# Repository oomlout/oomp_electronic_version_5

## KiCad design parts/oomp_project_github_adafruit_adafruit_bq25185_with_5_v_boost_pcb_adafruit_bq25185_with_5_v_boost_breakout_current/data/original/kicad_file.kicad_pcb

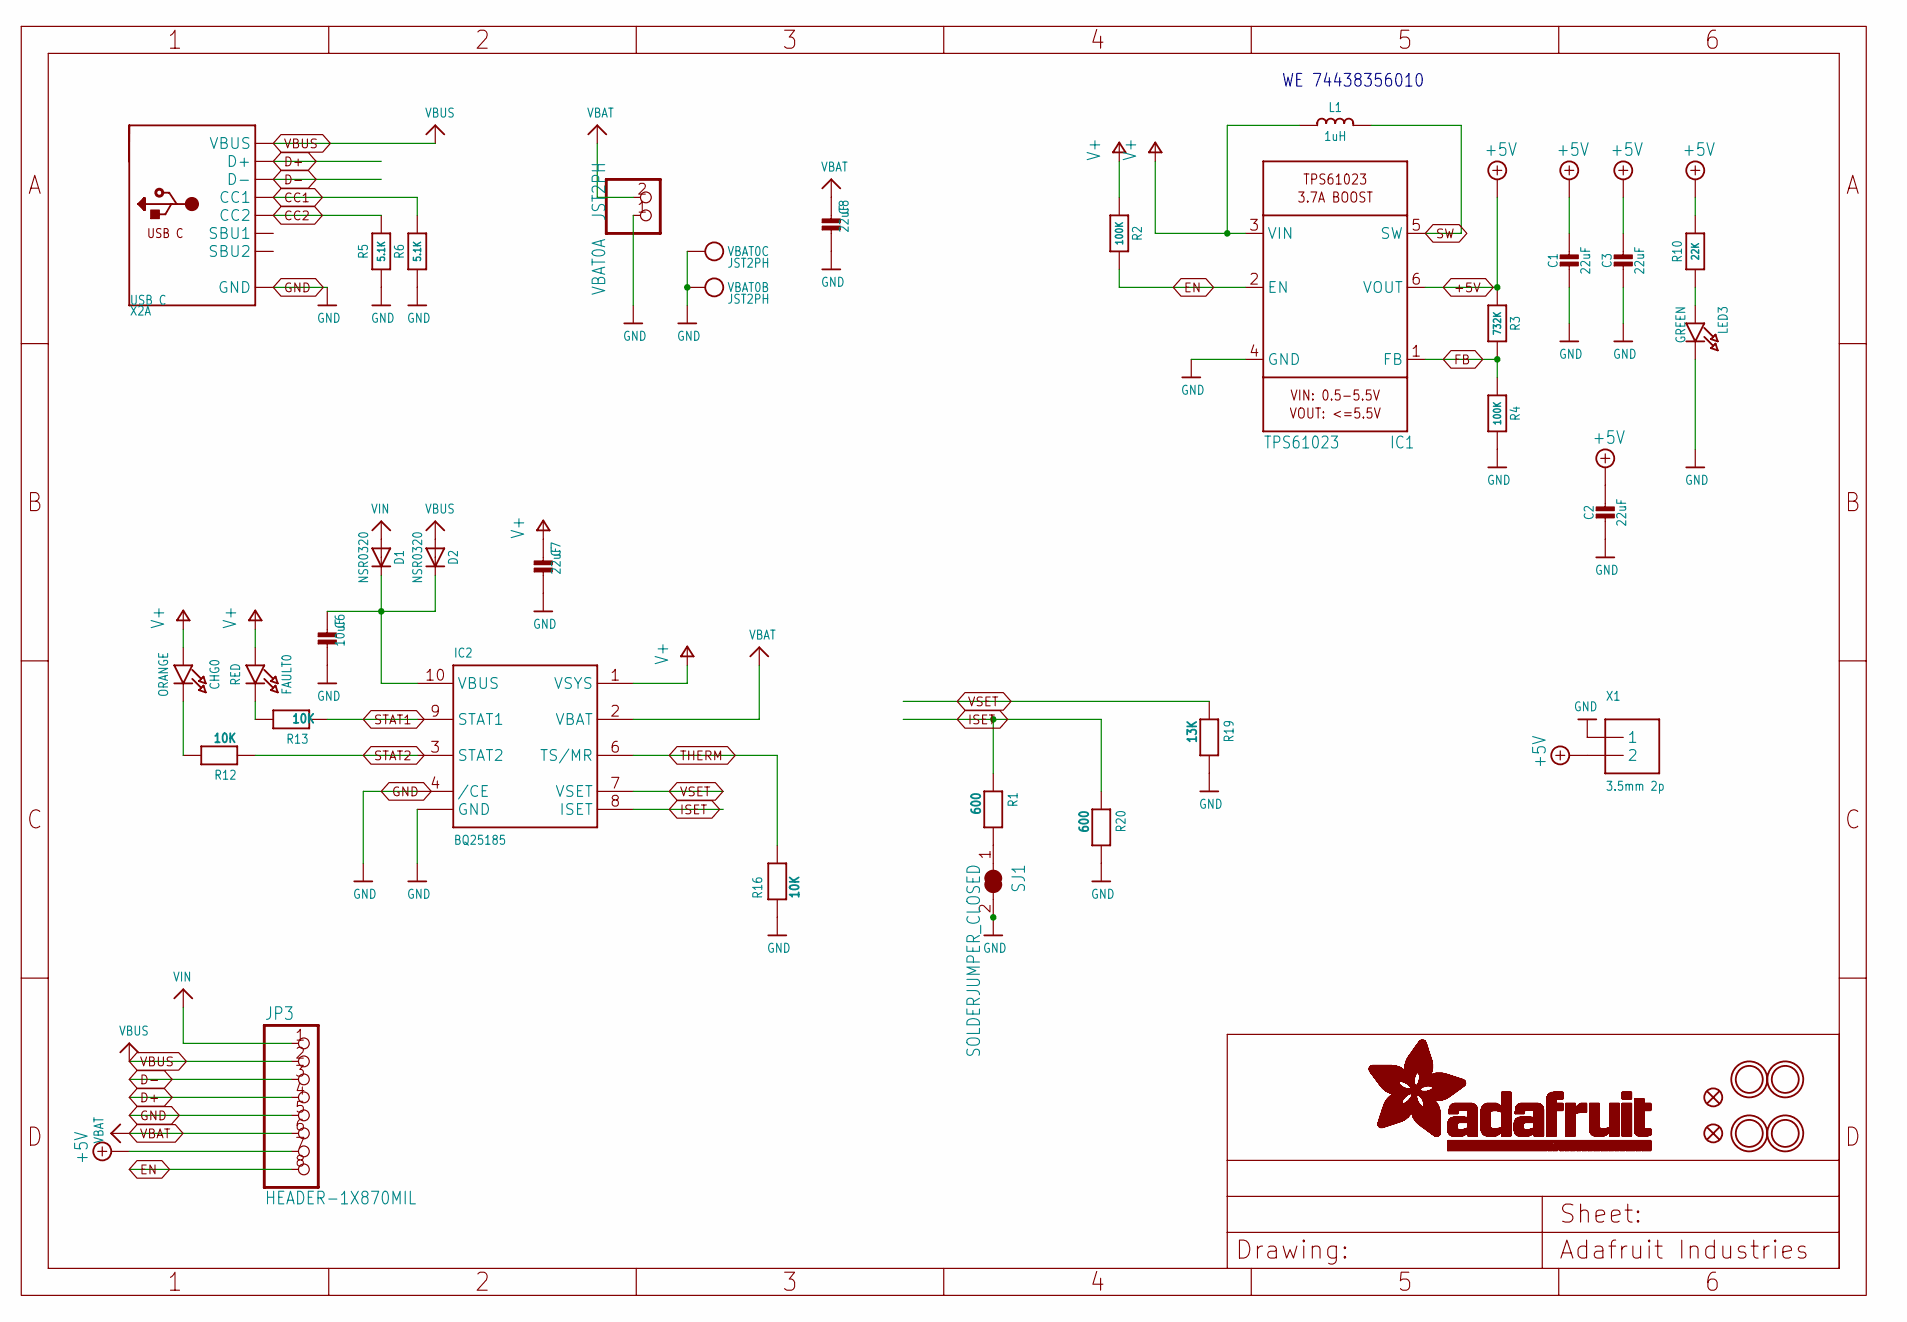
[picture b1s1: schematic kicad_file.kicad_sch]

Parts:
C1, C2, C3, C7, C8: 22uF; 0805-NO
C6: 10uF; 0805-NO
CHG0: ORANGE; CHIPLED_0603_NOOUTLINE
D1, D2: NSR0320; SOD-323_MINI
FAULT0: RED; CHIPLED_0603_NOOUTLINE
FID1, FID2: FIDUCIAL_0.5MM
IC1: TPS61023; SOT563
IC2: BQ25185; WSON10
JP3: HEADER-1X870MIL; 1X08_ROUND_70
L1: 1uH; INDUCTOR_5045_SMALLTABS
LED3: GREEN; CHIPLED_0603_NOOUTLINE
R1, R20: 600; _0402NO
R2, R4: 100K; _0402NO
R3: 732K; _0402NO
R5, R6: 5.1K; _0402NO
R10: 22K; _0402NO
R12, R13, R16: 10K; _0402NO
R19: 13K; _0402NO
SJ1: SOLDERJUMPER_CLOSED; SOLDERJUMPER_CLOSEDWIRE
U$9, U$10, U$11, U$12: MOUNTINGHOLE2.5; MOUNTINGHOLE_2.5_PLATED
VBAT0: JST2PH; JSTPH2_BATT; LCSC C47647
X1: 3.5mm 2p; TERMBLOCK_1X2-3.5MM
X2: USB C; USB_C_CUSB31-CFM2AX-01-X; LCSC C165948

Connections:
+5V: C1.1, C2.1, C3.1, IC1.6 (VOUT), JP3.7, R3.1, R10.2, X1.2
CC1: R6.2, X2.A5 (CC1)
CC2: R5.2, X2.B5 (CC2)
D+: JP3.4, X2.A6 (D+), X2.B6 (D+)
D-: JP3.3, X2.A7 (D-), X2.B7 (D-)
EN: IC1.2 (EN), JP3.8, R2.2
FB: IC1.1 (FB), R3.2, R4.1
GND: C1.2, C2.2, C3.2, C6.2, C7.2, C8.2, IC1.4 (GND), IC2.4 (/CE), IC2.5 (GND), IC2.PAD (GND), JP3.5, LED3.C, R4.2, R5.1, R6.1, R16.1, R19.2, R20.2, SJ1.2, VBAT0.1, VBAT0.NC1, VBAT0.NC2, X1.1, X2.A1B12 (GND), X2.B1A12 (GND)
ISET: IC2.8 (ISET), R1.1, R20.1
unnamed: R1.2, SJ1.1
unnamed: C6.1, D1.C, D2.C, IC2.10 (VBUS)
unnamed: CHG0.C, R12.2
unnamed: LED3.A, R10.1
unnamed: FAULT0.C, R13.2
STAT1: IC2.9 (STAT1), R13.1
STAT2: IC2.3 (STAT2), R12.1
SW: IC1.5 (SW), L1.2
THERM: IC2.6 (TS/MR), R16.2
V+: C7.1, CHG0.A, FAULT0.A, IC1.3 (VIN), IC2.1 (VSYS), L1.1, R2.1
VBAT: C8.1, IC2.2 (VBAT), JP3.6, VBAT0.2
VBUS: D2.A, JP3.2, X2.A4B9 (VBUS), X2.B4A9 (VBUS)
VIN: D1.A, JP3.1
VSET: IC2.7 (VSET), R19.1

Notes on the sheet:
WE 74438356010

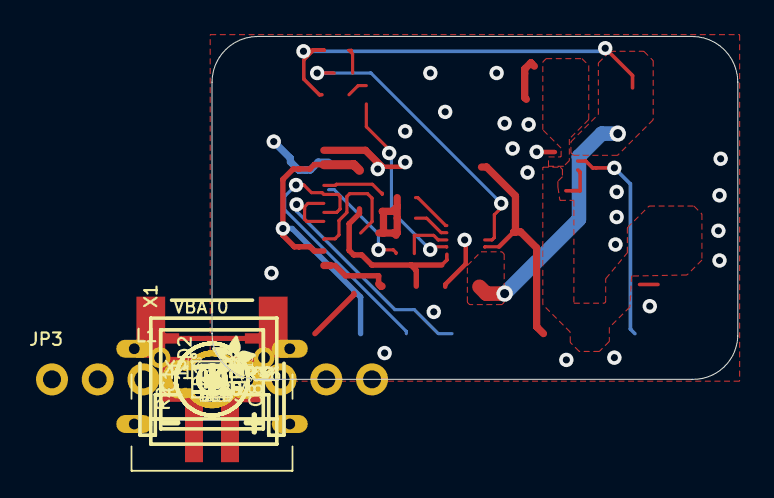
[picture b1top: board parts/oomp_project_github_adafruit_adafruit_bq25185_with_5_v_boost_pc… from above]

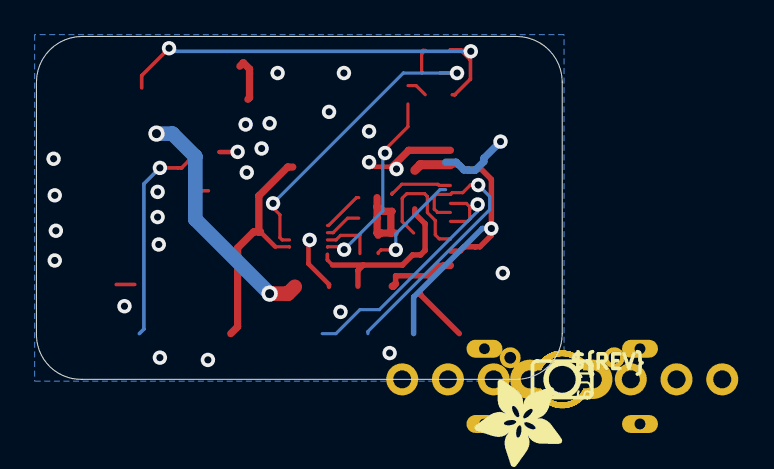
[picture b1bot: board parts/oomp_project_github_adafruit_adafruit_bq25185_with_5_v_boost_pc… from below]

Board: 2 copper layers, 29.2 x 19.1 mm, 66 parts (16 on the bottom side), 23 nets.

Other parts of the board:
PLABEL0: PLABEL0
PLABEL1: PLABEL1
PLABEL2: PLABEL2
PLABEL3: PLABEL3
PLABEL4: PLABEL4
PLABEL5: PLABEL5
PLABEL6: PLABEL6
PLABEL7: PLABEL7
PLABEL8: PLABEL8
PLABEL9: PLABEL9
PLABEL10: PLABEL10
PLABEL12: PLABEL12
PLABEL13: PLABEL13
PLABEL16: PLABEL16
PLABEL17: PLABEL17
PLABEL18: PLABEL18
PLABEL19: PLABEL19
PLABEL20: PLABEL20
PLABEL21: PLABEL21
PLABEL22: PLABEL22
PLABEL23: PLABEL23
PLABEL24: PLABEL24
PLABEL25: PLABEL25
PLABEL26: PLABEL26
U$2: PCBFEAT-REV-040
U$3: SYMBOL_PLUS
U$4: SYMBOL_MINUS
U$26: ADAFRUIT_5MM
U$34: ADAFRUIT_2.5MM

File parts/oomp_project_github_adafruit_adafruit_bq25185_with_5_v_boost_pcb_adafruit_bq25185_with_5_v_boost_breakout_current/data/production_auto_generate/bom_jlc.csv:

Comment,Designator,Footprint,LCSC Part #
,JP3,Adafruit bq25185 with 5V Boost Breakout-import-fps:1X08_ROUND_70,C492421
,U$34,Adafruit bq25185 with 5V Boost Breakout-import-fps:ADAFRUIT_2.5MM,
,U$26,Adafruit bq25185 with 5V Boost Breakout-import-fps:ADAFRUIT_5MM,
,U$2,Adafruit bq25185 with 5V Boost Breakout-import-fps:PCBFEAT-REV-040,
,PLABEL0,Adafruit bq25185 with 5V Boost Breakout-import-fps:PLABEL0,
,PLABEL1,Adafruit bq25185 with 5V Boost Breakout-import-fps:PLABEL1,
,PLABEL10,Adafruit bq25185 with 5V Boost Breakout-import-fps:PLABEL10,
,PLABEL12,Adafruit bq25185 with 5V Boost Breakout-import-fps:PLABEL12,
,PLABEL13,Adafruit bq25185 with 5V Boost Breakout-import-fps:PLABEL13,
,PLABEL16,Adafruit bq25185 with 5V Boost Breakout-import-fps:PLABEL16,
,PLABEL17,Adafruit bq25185 with 5V Boost Breakout-import-fps:PLABEL17,
,PLABEL18,Adafruit bq25185 with 5V Boost Breakout-import-fps:PLABEL18,
,PLABEL19,Adafruit bq25185 with 5V Boost Breakout-import-fps:PLABEL19,
,PLABEL2,Adafruit bq25185 with 5V Boost Breakout-import-fps:PLABEL2,
,PLABEL20,Adafruit bq25185 with 5V Boost Breakout-import-fps:PLABEL20,
,PLABEL21,Adafruit bq25185 with 5V Boost Breakout-import-fps:PLABEL21,
,PLABEL22,Adafruit bq25185 with 5V Boost Breakout-import-fps:PLABEL22,
,PLABEL23,Adafruit bq25185 with 5V Boost Breakout-import-fps:PLABEL23,
,PLABEL24,Adafruit bq25185 with 5V Boost Breakout-import-fps:PLABEL24,
,PLABEL25,Adafruit bq25185 with 5V Boost Breakout-import-fps:PLABEL25,
,PLABEL26,Adafruit bq25185 with 5V Boost Breakout-import-fps:PLABEL26,
,PLABEL3,Adafruit bq25185 with 5V Boost Breakout-import-fps:PLABEL3,
,PLABEL4,Adafruit bq25185 with 5V Boost Breakout-import-fps:PLABEL4,
,PLABEL5,Adafruit bq25185 with 5V Boost Breakout-import-fps:PLABEL5,
,PLABEL6,Adafruit bq25185 with 5V Boost Breakout-import-fps:PLABEL6,
,PLABEL7,Adafruit bq25185 with 5V Boost Breakout-import-fps:PLABEL7,
,PLABEL8,Adafruit bq25185 with 5V Boost Breakout-import-fps:PLABEL8,
,PLABEL9,Adafruit bq25185 with 5V Boost Breakout-import-fps:PLABEL9,
,U$4,Adafruit bq25185 with 5V Boost Breakout-import-fps:SYMBOL_MINUS,
,U$3,Adafruit bq25185 with 5V Boost Breakout-import-fps:SYMBOL_PLUS,
100K,"R2,R4",Adafruit bq25185 with 5V Boost Breakout-import-fps:_0402NO,C25530
10K,"R12,R13,R16",Adafruit bq25185 with 5V Boost Breakout-import-fps:_0402NO,C2906861
10uF,C6,Adafruit bq25185 with 5V Boost Breakout-import-fps:0805-NO,
13K,R19,Adafruit bq25185 with 5V Boost Breakout-import-fps:_0402NO,
1uH,L1,Adafruit bq25185 with 5V Boost Breakout-import-fps:INDUCTOR_5045_SMALLTABS,
22K,R10,Adafruit bq25185 with 5V Boost Breakout-import-fps:_0402NO,C82868
22uF,"C1,C2,C3,C7,C8",Adafruit bq25185 with 5V Boost Breakout-import-fps:0805-NO,
3.5mm 2p,X1,Adafruit bq25185 with 5V Boost Breakout-import-fps:TERMBLOCK_1X2-3.5MM,
5.1K,"R5,R6",Adafruit bq25185 with 5V Boost Breakout-import-fps:_0402NO,C25905
600,"R1,R20",Adafruit bq25185 with 5V Boost Breakout-import-fps:_0402NO,
732K,R3,Adafruit bq25185 with 5V Boost Breakout-import-fps:_0402NO,
BQ25185,IC2,Adafruit bq25185 with 5V Boost Breakout-import-fps:WSON10,
GREEN,LED3,Adafruit bq25185 with 5V Boost Breakout-import-fps:CHIPLED_0603_NOOUTLINE,
JST2PH,VBAT0,Adafruit bq25185 with 5V Boost Breakout-import-fps:JSTPH2_BATT,
NSR0320,"D1,D2",Adafruit bq25185 with 5V Boost Breakout-import-fps:SOD-323_MINI,
ORANGE,CHG0,Adafruit bq25185 with 5V Boost Breakout-import-fps:CHIPLED_0603_NOOUTLINE,
RED,FAULT0,Adafruit bq25185 with 5V Boost Breakout-import-fps:CHIPLED_0603_NOOUTLINE,
TPS61023,IC1,Adafruit bq25185 with 5V Boost Breakout-import-fps:SOT563,
USB C,X2,Adafruit bq25185 with 5V Boost Breakout-import-fps:USB_C_CUSB31-CFM2AX-01-X,

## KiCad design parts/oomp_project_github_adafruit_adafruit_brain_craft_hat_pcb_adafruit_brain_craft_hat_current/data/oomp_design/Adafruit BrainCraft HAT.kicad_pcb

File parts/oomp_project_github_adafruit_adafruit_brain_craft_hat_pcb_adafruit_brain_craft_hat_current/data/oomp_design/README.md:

# OOMP KiCad design copy

Open `Adafruit BrainCraft HAT.kicad_pro` (or the `.kicad_pcb` / `.kicad_sch`) in KiCad. Local OOMP libraries are under `libraries/`. Original inputs are preserved in [../original/](../original/).

Only verified unchanged installed KiCad defaults were renamed. Modified, custom, unmatched and unavailable items remain unchanged. Soldering variants are never swapped during conversion. Existing pad coordinates, nets and UUIDs are preserved.

See [conversion_report.yaml](conversion_report.yaml) for every conversion and skip. Copy this directory before editing; regeneration refuses to overwrite edited design files.

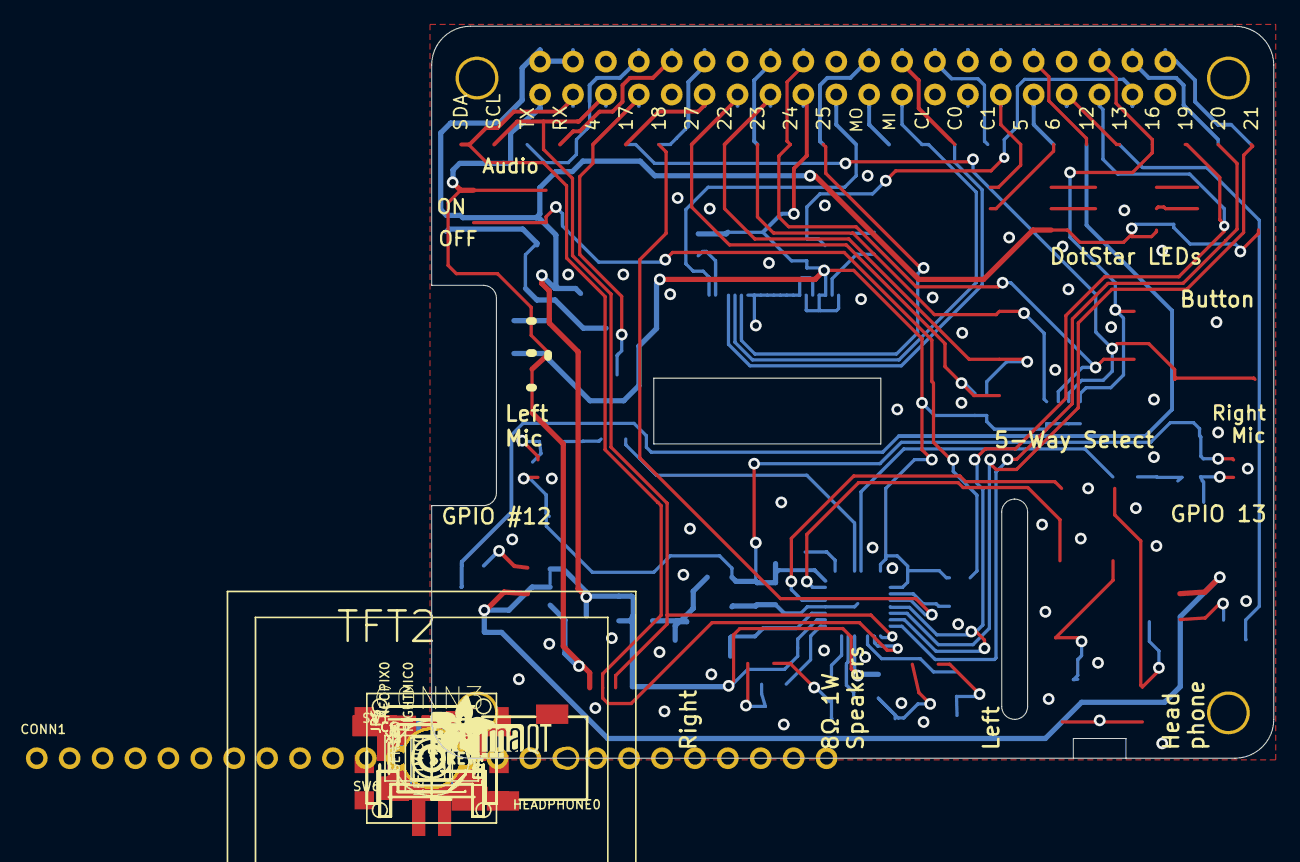
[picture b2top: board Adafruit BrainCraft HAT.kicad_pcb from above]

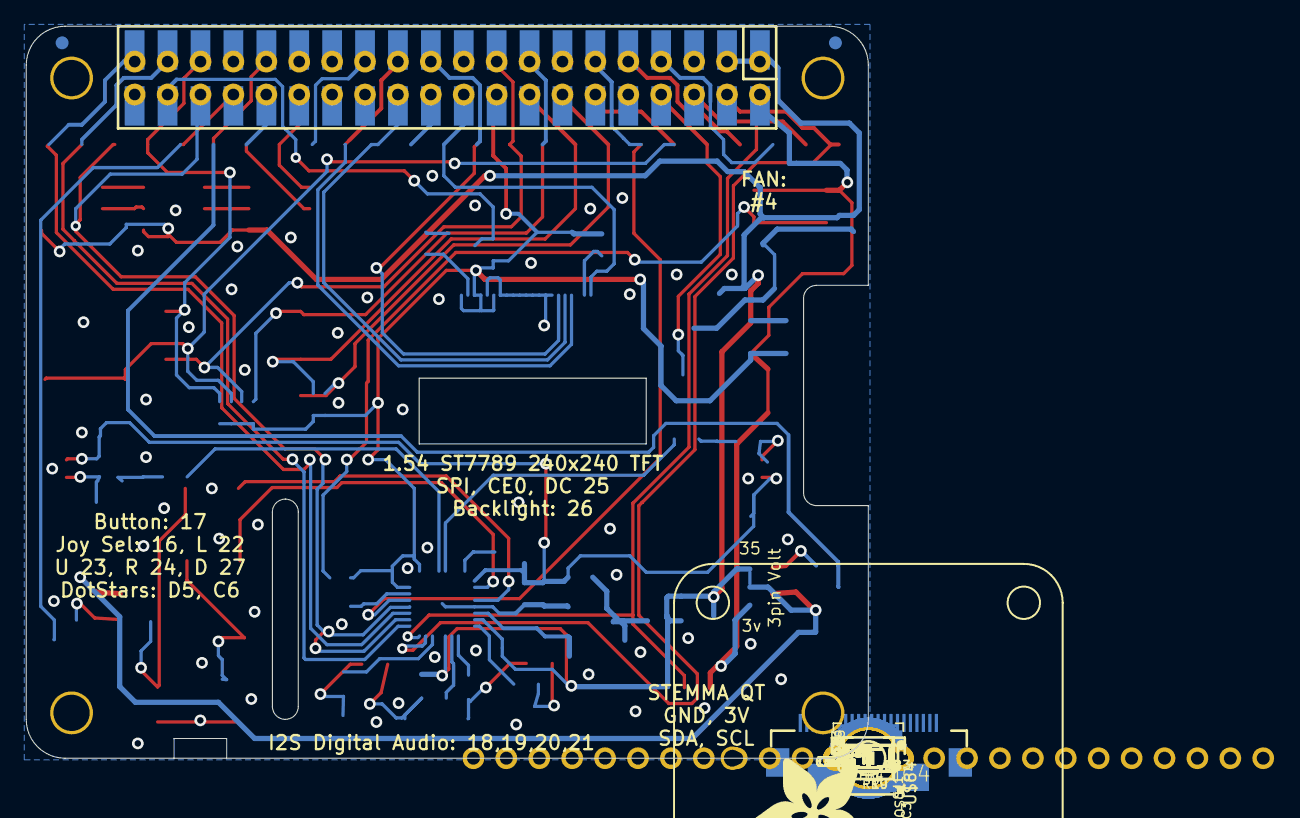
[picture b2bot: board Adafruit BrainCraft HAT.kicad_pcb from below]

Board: 2 copper layers, 65.0 x 56.5 mm, 95 parts (69 on the bottom side), 67 nets.

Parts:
C1, C2, C5, C9, C10, C11, C13, C15, C17, C23, C24, C32, C33, C34: 10uF; 0805-NO
C3, C7, C8, C12, C14, C16, C18, C25: 0.1uF; 0603-NO
C4, C6: 100uF; PANASONIC_C
C19, C20, C21, C22: 33pF; 0603-NO
C26, C27: 220pF; 0603-NO
C28, C29, C30, C31: 100pF; 0603-NO
CONN1: HEADER-1X25; 1X25_ROUND_70MIL
CONN3: STEMMA_I2C_QT; JST_SH4
D1, D2: 3.6V; SOD-323
D3: 1N4148; SOD-323
FB1, FB2: Ferrite; 0805
FB3, FB7, FB8, FB9, FB10: Ferrite; 0805-NO
FB4: FERRITE; 0805-NO
FID1, FID2: FIDUCIAL_1MM
HEADPHONE0: 4UCONN_18510
IC3: WM8960; QFN32_5MM
IC4: APX803-SAG; SOT23
JP4, JP5: 1X03_ROUND_76
LED1, LED2, LED3: SK6822; APA102
LEFTMIC0: SPW2430HR5H-B
NEOPIX0: JST PH 3; JSTPH3
OSC1: ECS-3225MV; OSC_3.2X2.5MM
Q1, Q3: BSS138; SOT23-WIDE
R1, R2, R3, R4: 10K; 0603-NO
R5: 10; 0603-NO
R6: 10k; 0603-NO
R7, R8: 1K; 0603-NO
R9, R10: 10K; RESPACK_4X0603
RIGHTMIC0: SPW2430HR5H-B
RPI1: RASPBERRYPI_BPLUS_HAT_SMTTHM_SLOTS; PI_HAT_SMTTHM_SLOTS
SENSE0: JST PH 3; JSTPH3
SJ1: SOLDERJUMPER_2WAY_OPEN_NOPASTE
SW1: EVQQ; EVQ-Q2_SMALLER
SW5: NAVSWITCHSKQUABAUE010; SKQUBAE010
SW6: EG1390
TFT2: DISP_TFT_1.54IN_240X240_22P; TFT_1.54IN_240X240_22PIN
TP1, TP2, TP3, TP4: SEWTAP_SMTNUTM3; SMT_NUT_3MM
TP6: TESTPOINT_ROUND_2MM
U3: AP2112-3.3K; SOT23-5
U$11: PCBFEAT-REV-040
U$72: STEMMAQT
U$75: ADAFRUIT_5MM
U$79: BRAINPAD_1IN
U$82: FAN_30X30MM
U$84: CON_MOLEX_2P; 53398-0271
U$87: ADAFRUIT_9MM
X1, X5: JSTPH 2P; JSTPH2

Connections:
3.3V: C12.1, CONN3.2, IC3.8, IC3.10, IC4.3, JP4.2, JP5.2, OSC1.4, R1.2, R2.2, R9.5, R9.6, R9.7, R9.8, R10.7, R10.8, RPI1.1, RPI1.17, RPI1.S1, RPI1.S17, SJ1.3, SW6.S1, SW6.S2, TFT2.1, TFT2.3, TFT2.4, TFT2.6
5.0V: C9.1, C10.1, C11.1, C32.1, C33.1, D3.C, IC3.21, IC3.26, JP4.3, JP5.3, LED1.4, LED2.4, LED3.4, RPI1.2, RPI1.4, RPI1.S2, RPI1.S4, SJ1.1, U3.1, U3.3, U$84.1
AGND: C3.2, C5.2, FB2.1, IC3.28, IC3.33
AVDD: C3.1, C5.1, C15.1, C16.1, C17.1, C18.1, C25.1, FB1.1, IC3.32, LEFTMIC0.4, RIGHTMIC0.4
BUTTON: CONN1.6, R9.3, RPI1.11, RPI1.S11, SW1.B, SW1.B'
EECLK: RPI1.28, RPI1.S28
EEDATA: RPI1.27, RPI1.S27
FAN: CONN1.5, Q1.1, R3.1, RPI1.7, RPI1.S7
GND: C1.2, C2.2, C7.2, C8.2, C9.2, C10.2, C11.2, C12.2, C13.2, C14.2, C15.2, C16.2, C17.2, C18.2, C19.2, C20.2, C21.2, C22.2, C25.2, C26.2, C27.2, C28.2, C29.2, C30.2, C31.2, C32.2, C33.2, C34.2, CONN3.1, D1.A, D2.A, FB2.2, HEADPHONE0.1-GND, HEADPHONE0.4-INNER_SLEEVE, IC3.9, IC3.20, IC3.24, IC4.1, JP4.1, JP5.1, LED1.3, LED2.3, LED3.3, LEFTMIC0.2, LEFTMIC0.3, NEOPIX0.1, OSC1.2, Q1.2, Q3.2, R3.2, R4.1, R6.1, RIGHTMIC0.2, RIGHTMIC0.3, RPI1.6, RPI1.9, RPI1.14, RPI1.20, RPI1.25, RPI1.30, RPI1.34, RPI1.39, RPI1.S6, RPI1.S9, RPI1.S14, RPI1.S20, RPI1.S25, RPI1.S30, RPI1.S34, RPI1.S39, SENSE0.1, SW1.A, SW1.A', SW5.4, SW6.O1, SW6.O2, TFT2.5, TFT2.7, TFT2.8, TFT2.9, TFT2.10, TFT2.11, TFT2.12, TFT2.13, TFT2.14, TFT2.15, TFT2.22, TFT2.SUPPORT1, TFT2.SUPPORT2, TP1.P$1, TP2.P$1, TP3.P$1, TP4.P$1, U3.2
I2S_BCLK: CONN1.7, IC3.12, RPI1.12, RPI1.S12
I2S_DIN: CONN1.24, IC3.16, RPI1.38, RPI1.S38
I2S_DOUT: CONN1.25, IC3.14, RPI1.40, RPI1.S40
I2S_LRCLK: CONN1.23, IC3.13, IC3.15, RPI1.35, RPI1.S35
JOY_D: CONN1.8, R10.1, RPI1.13, RPI1.S13, SW5.3
JOY_IN: CONN1.22, R9.4, RPI1.36, RPI1.S36, SW5.6
JOY_L: CONN1.9, R10.2, RPI1.15, RPI1.S15, SW5.2
JOY_R: CONN1.11, R9.2, RPI1.18, RPI1.S18, SW5.5
JOY_U: CONN1.10, R9.1, RPI1.16, RPI1.S16, SW5.1
LEDC: CONN1.19, LED1.2, RPI1.31, RPI1.S31
LEDD: CONN1.18, LED1.1, RPI1.29, RPI1.S29
LEDK: R5.2, TFT2.2
LINPUT1: C23.2, IC3.4
LITE: Q3.1, R2.1, RPI1.37, RPI1.S37
LSTEMMA: NEOPIX0.3, R7.1
MCLK: IC3.11, OSC1.3
MCLK_EN: OSC1.1, SW6.P1, SW6.P2
MICBIAS: C2.1, C8.1, IC3.1
unnamed: FB7.1, IC3.19
unnamed: FB8.1, IC3.22
unnamed: C6.+, IC3.31
unnamed: Q3.3, R5.1
unnamed: C4.+, IC3.29
unnamed: LED1.6, LED2.1
unnamed: C4.-, C27.1, HEADPHONE0.3-OUTER_SLEEVE, R4.2
unnamed: C6.-, C26.1, HEADPHONE0.2-TIP, R6.2
unnamed: LED1.5, LED2.2
unnamed: C19.1, FB3.1, RIGHTMIC0.1
unnamed: C20.1, FB4.1, LEFTMIC0.1
unnamed: LED2.6, LED3.1
unnamed: LED2.5, LED3.2
unnamed: C21.1, C24.1, FB3.2
unnamed: C22.1, C23.1, FB4.2
unnamed: D3.A, Q1.3, TP6.P$1, U$84.2
unnamed: FB9.1, IC3.25
unnamed: FB10.1, IC3.23
OUT: C13.1, C14.1, FB1.2, U3.5
PWM0: CONN1.20, D1.C, R7.2, RPI1.32, RPI1.S32
PWM1: CONN1.21, D2.C, R8.2, RPI1.33, RPI1.S33
RINPUT1: C24.2, IC3.5
RSTEMMA: R8.1, SENSE0.3
RXD: CONN1.4, RPI1.10, RPI1.S10
SCL: CONN1.2, CONN3.4, IC3.17, RPI1.5, RPI1.S5
SDA: CONN1.1, CONN3.3, IC3.18, RPI1.3, RPI1.S3
SPI_CE1: CONN1.17, RPI1.26, RPI1.S26
SPI_MISO: CONN1.14, RPI1.21, RPI1.S21
SPK_LN: C31.1, FB10.2, X1.1
SPK_LP: C30.1, FB9.2, X1.2
SPK_RN: C28.1, FB7.2, X5.1
SPK_RP: C29.1, FB8.2, X5.2
TFT_CS: CONN1.16, RPI1.24, RPI1.S24, TFT2.18
TFT_DC: CONN1.12, RPI1.22, RPI1.S22, TFT2.16
TFT_MOSI: CONN1.13, RPI1.19, RPI1.S19, TFT2.21
TFT_RESET: IC4.2, R1.1, TFT2.20
TFT_SCLK: CONN1.15, RPI1.23, RPI1.S23, TFT2.17
TXD: CONN1.3, RPI1.8, RPI1.S8
VCC: C34.1, NEOPIX0.2, SENSE0.2, SJ1.2
VMID: C1.1, C7.1, IC3.27

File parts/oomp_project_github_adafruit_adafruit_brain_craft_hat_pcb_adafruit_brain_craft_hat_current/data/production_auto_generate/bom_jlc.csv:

Comment,Designator,Footprint,LCSC Part #
,"JP4,JP5",Adafruit BrainCraft HAT-import-fps:1X03_ROUND_76,C49257
,HEADPHONE0,Adafruit BrainCraft HAT-import-fps:4UCONN_18510,
,U$75,Adafruit BrainCraft HAT-import-fps:ADAFRUIT_5MM,
,U$87,Adafruit BrainCraft HAT-import-fps:ADAFRUIT_9MM,
,U$79,Adafruit BrainCraft HAT-import-fps:BRAINPAD_1IN,
,U$82,Adafruit BrainCraft HAT-import-fps:FAN_30X30MM,
,U$11,Adafruit BrainCraft HAT-import-fps:PCBFEAT-REV-040,
,"LEFTMIC0,RIGHTMIC0",Adafruit BrainCraft HAT-import-fps:SPW2430HR5H-B,
,U$72,Adafruit BrainCraft HAT-import-fps:STEMMAQT,
,TP6,Adafruit BrainCraft HAT-import-fps:TESTPOINT_ROUND_2MM,
0.1uF,"C3,C7,C8,C12,C14,C16,C18,C25",Adafruit BrainCraft HAT-import-fps:0603-NO,C14663
10,R5,Adafruit BrainCraft HAT-import-fps:0603-NO,C22859
100pF,"C28,C29,C30,C31",Adafruit BrainCraft HAT-import-fps:0603-NO,
100uF,"C4,C6",Adafruit BrainCraft HAT-import-fps:PANASONIC_C,
10K,"R1,R2,R3,R4",Adafruit BrainCraft HAT-import-fps:0603-NO,C98220
10k,R6,Adafruit BrainCraft HAT-import-fps:0603-NO,C98220
10K,"R9,R10",Adafruit BrainCraft HAT-import-fps:RESPACK_4X0603,C98220
10uF,"C1,C2,C5,C9,C10,C11,C13,C15,C17,C23,C24,C32,C33,C34",Adafruit BrainCraft HAT-import-fps:0805-NO,
1K,"R7,R8",Adafruit BrainCraft HAT-import-fps:0603-NO,C2907002
1N4148,D3,Adafruit BrainCraft HAT-import-fps:SOD-323,
220pF,"C26,C27",Adafruit BrainCraft HAT-import-fps:0603-NO,
3.6V,"D1,D2",Adafruit BrainCraft HAT-import-fps:SOD-323,
33pF,"C19,C20,C21,C22",Adafruit BrainCraft HAT-import-fps:0603-NO,C107047
AP2112-3.3K,U3,Adafruit BrainCraft HAT-import-fps:SOT23-5,
APX803-SAG,IC4,Adafruit BrainCraft HAT-import-fps:SOT23,
BSS138,"Q1,Q3",Adafruit BrainCraft HAT-import-fps:SOT23-WIDE,C52895
CON_MOLEX_2P,U$84,Adafruit BrainCraft HAT-import-fps:53398-0271,
DISP_TFT_1.54IN_240X240_22P,TFT2,Adafruit BrainCraft HAT-import-fps:TFT_1.54IN_240X240_22PIN,
ECS-3225MV,OSC1,Adafruit BrainCraft HAT-import-fps:OSC_3.2X2.5MM,
EG1390,SW6,Adafruit BrainCraft HAT-import-fps:EG1390,
EVQQ,SW1,Adafruit BrainCraft HAT-import-fps:EVQ-Q2_SMALLER,
Ferrite,"FB1,FB2",Adafruit BrainCraft HAT-import-fps:0805,
Ferrite,"FB3,FB7,FB8,FB9,FB10",Adafruit BrainCraft HAT-import-fps:0805-NO,
FERRITE,FB4,Adafruit BrainCraft HAT-import-fps:0805-NO,
HEADER-1X25,CONN1,Adafruit BrainCraft HAT-import-fps:1X25_ROUND_70MIL,C2883713
JST PH 3,"NEOPIX0,SENSE0",Adafruit BrainCraft HAT-import-fps:JSTPH3,
JSTPH 2P,"X1,X5",Adafruit BrainCraft HAT-import-fps:JSTPH2,
NAVSWITCHSKQUABAUE010,SW5,Adafruit BrainCraft HAT-import-fps:SKQUBAE010,
RASPBERRYPI_BPLUS_HAT_SMTTHM_SLOTS,RPI1,Adafruit BrainCraft HAT-import-fps:PI_HAT_SMTTHM_SLOTS,
SK6822,"LED1,LED2,LED3",Adafruit BrainCraft HAT-import-fps:APA102,
STEMMA_I2C_QT,CONN3,Adafruit BrainCraft HAT-import-fps:JST_SH4,C160404
WM8960,IC3,Adafruit BrainCraft HAT-import-fps:QFN32_5MM,

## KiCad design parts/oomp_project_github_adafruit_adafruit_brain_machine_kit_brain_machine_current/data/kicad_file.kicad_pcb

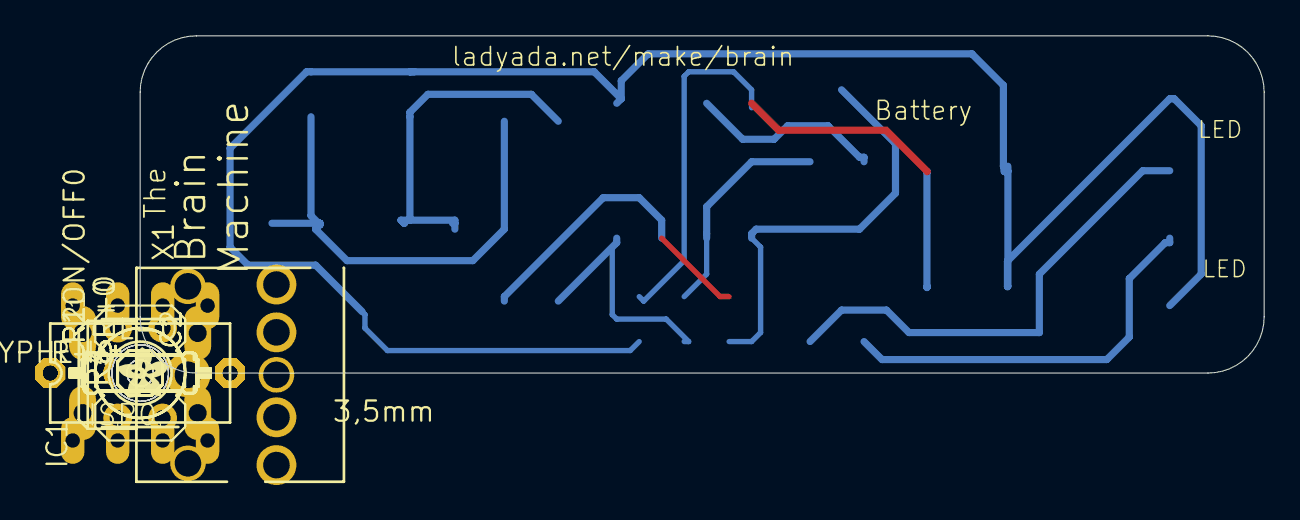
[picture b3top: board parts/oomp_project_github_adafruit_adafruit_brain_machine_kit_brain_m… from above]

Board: 16 copper layers, 63.5 x 19.1 mm, 27 parts (0 on the bottom side), 11 nets.

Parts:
+0: 1X01
C1, C2: 1.0uF; E2,5-5
HYPHEN0: 1X01
IC1: ATTINY25-20P; DIL08
ISP0: AVRISP-6; AVRISP
L+0: 1X01
L-0: 1X01
ON/OFF0: B3F-10XX
R1, R2: 1.0k; 0207_10
R3, R4: 47ohm; 0207_10
R+0: 1X01
R-0: 1X01
U$1: ADAFRUIT200MIL
UNK_HOLE_0: dummyfp0
UNK_HOLE_1: dummyfp1
UNK_HOLE_2: dummyfp2
UNK_HOLE_3: dummyfp3
UNK_HOLE_4: dummyfp4
UNK_HOLE_5: dummyfp5
UNK_HOLE_6: dummyfp6
UNK_HOLE_7: dummyfp7
UNK_HOLE_8: dummyfp8
UNK_HOLE_9: dummyfp9
X1: STEREOJACK; STX3100

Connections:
GND: C1.-, C2.-, HYPHEN0.1, IC1.4, ISP0.6, L-0.1, ON/OFF0.3, ON/OFF0.4, R-0.1, X1.1
LEYE+: L+0.1, R4.2
MISO: IC1.6, ISP0.1, R2.1
MOSI: IC1.5, ISP0.4, R1.1
unnamed: C1.+, R1.2, X1.4, X1.5
unnamed: C2.+, R2.2, X1.2, X1.3
unnamed: IC1.2, R4.1
unnamed: R3.2, R+0.1
RST: IC1.1, ISP0.5, ON/OFF0.1, ON/OFF0.2
SCK: IC1.7, ISP0.3, R3.1
VCC: +0.1, IC1.8, ISP0.2

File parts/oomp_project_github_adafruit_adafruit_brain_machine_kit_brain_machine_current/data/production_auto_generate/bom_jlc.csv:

Comment,Designator,Footprint,LCSC Part #
,"+0,L+0,L-0,R+0,R-0",brain-import-fps:1X01,
,HYPHEN0,brain-import-fps:1X01,C7501259
,U$1,brain-import-fps:ADAFRUIT200MIL,
,ON/OFF0,brain-import-fps:B3F-10XX,
1.0k,"R1,R2",brain-import-fps:0207_10,
1.0uF,"C1,C2","brain-import-fps:E2,5-5",
47ohm,"R3,R4",brain-import-fps:0207_10,
ATTINY25-20P,IC1,brain-import-fps:DIL08,
AVRISP-6,ISP0,brain-import-fps:AVRISP,
STEREOJACK,X1,brain-import-fps:STX3100,

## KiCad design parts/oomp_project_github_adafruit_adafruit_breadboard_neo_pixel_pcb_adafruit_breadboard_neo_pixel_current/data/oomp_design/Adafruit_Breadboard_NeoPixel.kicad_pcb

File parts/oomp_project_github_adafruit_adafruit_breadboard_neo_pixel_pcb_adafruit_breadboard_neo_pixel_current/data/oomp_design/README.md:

# OOMP KiCad design copy

Open `Adafruit_Breadboard_NeoPixel.kicad_pro` (or the `.kicad_pcb` / `.kicad_sch`) in KiCad. Local OOMP libraries are under `libraries/`. Original inputs are preserved in [../original/](../original/).

Only verified unchanged installed KiCad defaults were renamed. Modified, custom, unmatched and unavailable items remain unchanged. Soldering variants are never swapped during conversion. Existing pad coordinates, nets and UUIDs are preserved.

See [conversion_report.yaml](conversion_report.yaml) for every conversion and skip. Copy this directory before editing; regeneration refuses to overwrite edited design files.

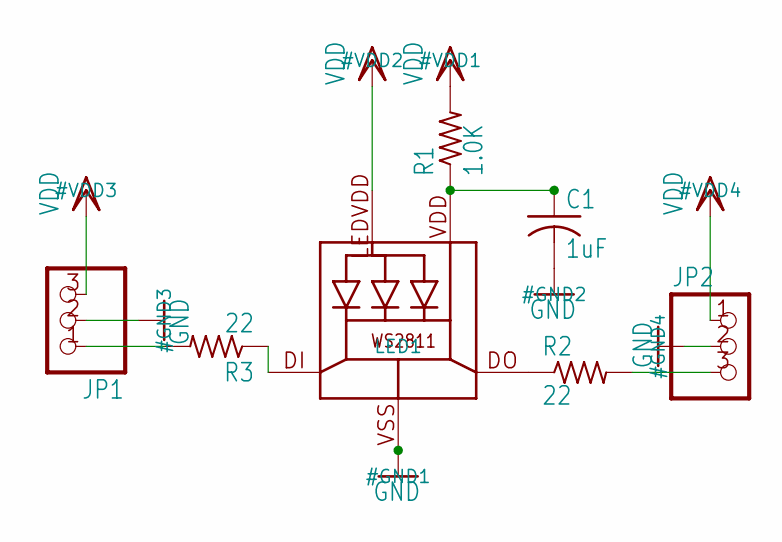
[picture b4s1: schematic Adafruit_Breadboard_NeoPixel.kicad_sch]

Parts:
C1: 1uF; C0603K
JP1, JP2: PINHD-1X3CB; 1X03-CLEANBIG
LED1: WS28115050
R1: 1.0K; R0603
R2, R3: 22; R0603

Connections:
GND: C1.2, JP1.2, JP2.2, LED1.VSS (GND)
IN: JP1.1, R3.2
unnamed: LED1.DO, R2.1
unnamed: LED1.DI, R3.1
unnamed: C1.1, LED1.VDD, R1.1
OUT: JP2.3, R2.2
VDD: JP1.3, JP2.1, LED1.LEDVDD, R1.2

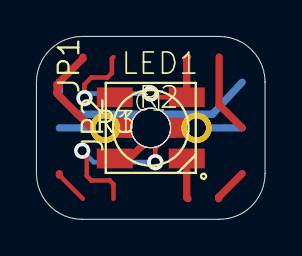
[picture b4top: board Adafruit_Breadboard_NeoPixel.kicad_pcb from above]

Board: 16 copper layers, 12.7 x 10.2 mm, 10 parts (1 on the bottom side), 7 nets.

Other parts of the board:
U$1: ADAFRUIT_2.5MM
UNK_HOLE_0: dummyfp0
UNK_HOLE_1: dummyfp1

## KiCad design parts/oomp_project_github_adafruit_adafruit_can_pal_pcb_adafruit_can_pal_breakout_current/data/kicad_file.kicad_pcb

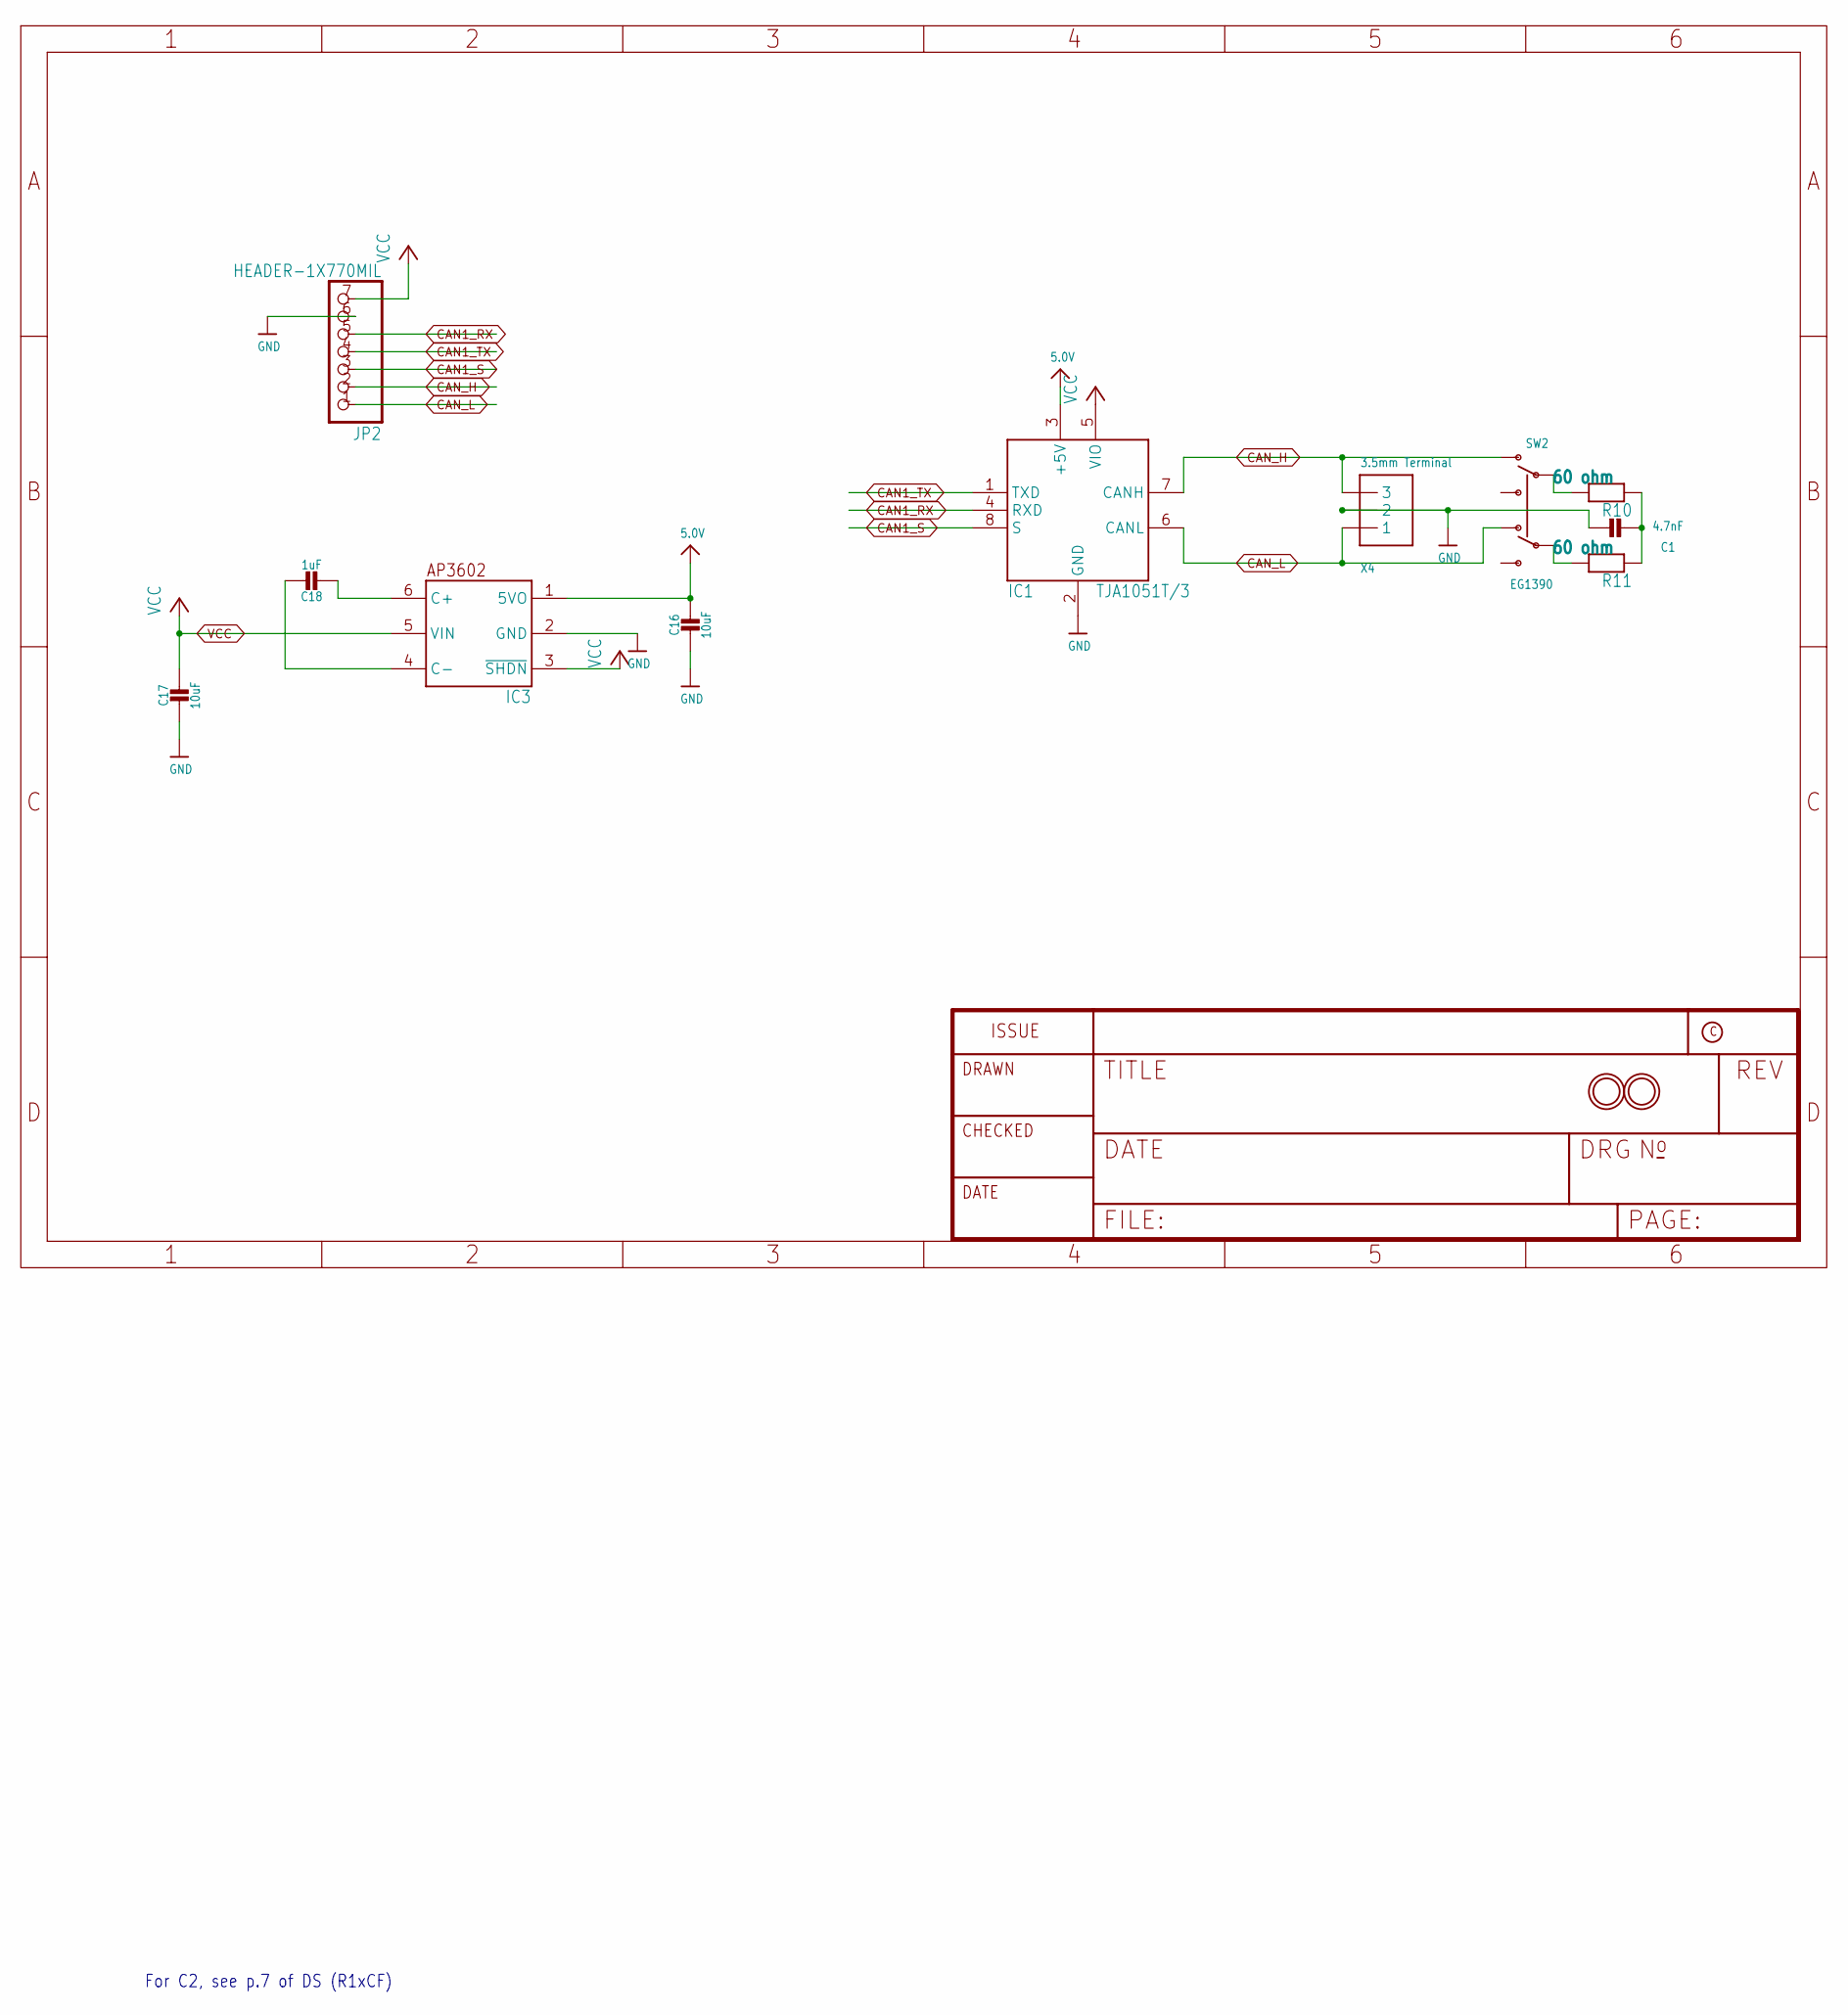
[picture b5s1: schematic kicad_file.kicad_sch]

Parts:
C1: 4.7nF; 0603-NO
C16, C17: 10uF; 0805-NO
C18: 1uF; 0805_10MGAP
IC1: TJA1051T/3; SOIC8_150MIL
IC3: AP3602; SOT23-6
JP2: HEADER-1X770MIL; 1X07_ROUND_70
R10, R11: 60 ohm; 0603-NO
SW2: EG1390; LCSC C2837066
U$2, U$3: MOUNTINGHOLE2.5; MOUNTINGHOLE_2.5_PLATED
X4: 3.5mm Terminal; TERMBLOCK_1X3-3.5MM

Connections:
5.0V: C16.1, IC1.3 (+5V), IC3.1 (5VO)
CAN1_RX: IC1.4 (RXD), JP2.5
CAN1_S: IC1.8 (S), JP2.3
CAN1_TX: IC1.1 (TXD), JP2.4
CAN_H: IC1.7 (CANH), JP2.2, SW2.O1, X4.3
CAN_L: IC1.6 (CANL), JP2.1, SW2.O2, X4.1
GND: C1.2, C16.2, C17.2, IC1.2 (GND), IC3.2 (GND), JP2.6, X4.2
unnamed: R10.2, SW2.P1
unnamed: R11.2, SW2.P2
unnamed: C18.2, IC3.6 (C+)
unnamed: C18.1, IC3.4 (C-)
unnamed: C1.1, R10.1, R11.1
VCC: C17.1, IC1.5 (VIO), IC3.3 (~SHDN), IC3.5 (VIN), JP2.7

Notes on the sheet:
For C2, see p.7 of DS (R1xCF)

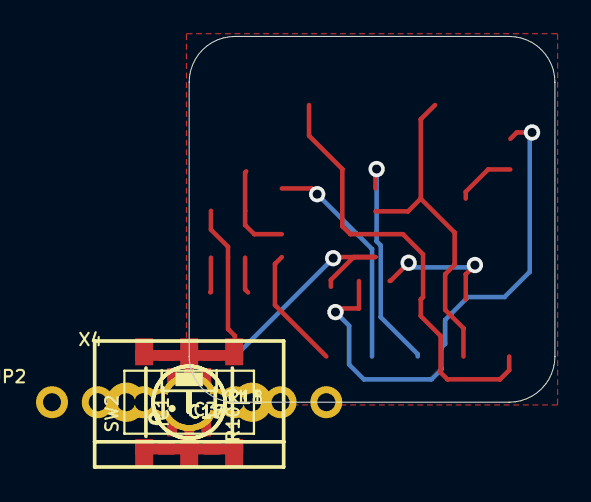
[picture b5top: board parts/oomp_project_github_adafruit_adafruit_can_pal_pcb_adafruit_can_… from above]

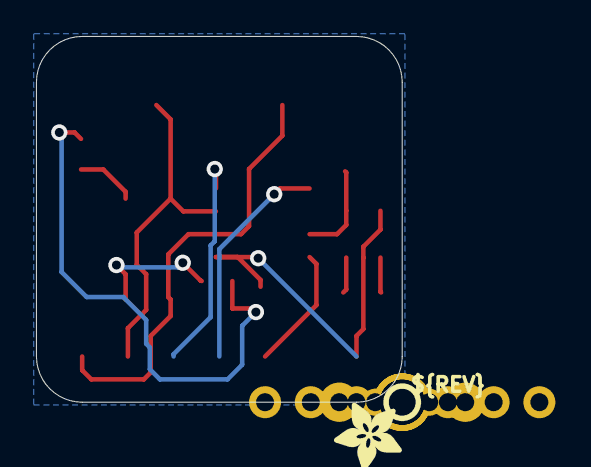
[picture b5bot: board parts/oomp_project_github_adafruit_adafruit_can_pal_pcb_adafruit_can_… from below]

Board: 2 copper layers, 20.3 x 20.3 mm, 30 parts (5 on the bottom side), 13 nets.

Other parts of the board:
PLABEL0: PLABEL0
PLABEL1: PLABEL1
PLABEL2: PLABEL2
PLABEL3: PLABEL3
PLABEL4: PLABEL4
PLABEL5: PLABEL5
PLABEL6: PLABEL6
PLABEL7: PLABEL7
PLABEL8: PLABEL8
PLABEL9: PLABEL9
PLABEL10: PLABEL10
PLABEL11: PLABEL11
PLABEL12: PLABEL12
PLABEL13: PLABEL13
PLABEL14: PLABEL14
U$6: ADAFRUIT_3.5MM
U$7: PCBFEAT-REV-040

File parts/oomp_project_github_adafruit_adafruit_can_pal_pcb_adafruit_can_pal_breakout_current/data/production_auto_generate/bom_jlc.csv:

Comment,Designator,Footprint,LCSC Part #
,JP2,Adafruit CAN Pal Breakout-import-fps:1X07_ROUND_70,C7501585
,U$6,Adafruit CAN Pal Breakout-import-fps:ADAFRUIT_3.5MM,
,U$7,Adafruit CAN Pal Breakout-import-fps:PCBFEAT-REV-040,
,PLABEL0,Adafruit CAN Pal Breakout-import-fps:PLABEL0,
,PLABEL1,Adafruit CAN Pal Breakout-import-fps:PLABEL1,
,PLABEL10,Adafruit CAN Pal Breakout-import-fps:PLABEL10,
,PLABEL11,Adafruit CAN Pal Breakout-import-fps:PLABEL11,
,PLABEL12,Adafruit CAN Pal Breakout-import-fps:PLABEL12,
,PLABEL13,Adafruit CAN Pal Breakout-import-fps:PLABEL13,
,PLABEL14,Adafruit CAN Pal Breakout-import-fps:PLABEL14,
,PLABEL2,Adafruit CAN Pal Breakout-import-fps:PLABEL2,
,PLABEL3,Adafruit CAN Pal Breakout-import-fps:PLABEL3,
,PLABEL4,Adafruit CAN Pal Breakout-import-fps:PLABEL4,
,PLABEL5,Adafruit CAN Pal Breakout-import-fps:PLABEL5,
,PLABEL6,Adafruit CAN Pal Breakout-import-fps:PLABEL6,
,PLABEL7,Adafruit CAN Pal Breakout-import-fps:PLABEL7,
,PLABEL8,Adafruit CAN Pal Breakout-import-fps:PLABEL8,
,PLABEL9,Adafruit CAN Pal Breakout-import-fps:PLABEL9,
10uF,"C16,C17",Adafruit CAN Pal Breakout-import-fps:0805-NO,
1uF,C18,Adafruit CAN Pal Breakout-import-fps:0805_10MGAP,
3.5mm Terminal,X4,Adafruit CAN Pal Breakout-import-fps:TERMBLOCK_1X3-3.5MM,
4.7nF,C1,Adafruit CAN Pal Breakout-import-fps:0603-NO,
60 ohm,"R10,R11",Adafruit CAN Pal Breakout-import-fps:0603-NO,
AP3602,IC3,Adafruit CAN Pal Breakout-import-fps:SOT23-6,
EG1390,SW2,Adafruit CAN Pal Breakout-import-fps:EG1390,
TJA1051T/3,IC1,Adafruit CAN Pal Breakout-import-fps:SOIC8_150MIL,
